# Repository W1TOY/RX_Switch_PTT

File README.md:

# RX Switch PTT — RF-sensing TX/RX antenna switch

A KiCad 9 project for a through-hole TX/RX antenna switch for amateur radio, **1.8–50 MHz, 100 W**.
The radio normally connects to a separate **RX antenna**; on PTT or detected RF it switches to the
**TX antenna** using PIN-style diodes, with a relay bypass for low-loss transmit.

## How it works

- **RF path** — Series/shunt diode switch (D1–D3, 1N4007 as PIN substitutes) with ~120 mA bias,
  RF chokes L1–L4 (~47 µH on FT50-43) and 1 kV MKP/C0G coupling capacitors.
- **PTT** — PTT IN (five RCA inputs in parallel) drives K1 (audio mute + dry-contact PTT OUT)
  and K2, a G2RL-2 relay that bypasses the diode TX path. K2 is always cold-switched because the
  diode path is already conducting.
- **RF sense** — Fast detector (LM311, < 1 µs) forces TX the moment RF appears. RF without PTT is
  treated as a fault: TX is held ~10 s after the last RF and the **RF SENSED** LED lights.
- **RX diode bias** — D3 is reverse-biased from an RF-derived high-voltage doubler
  (HT ≈ 2 × RF peak, clamped at ~220 V), so no separate HV supply is needed.
- **Fail-safe** — K3 (G2RL-2 DPDT) connects RADIO straight to the TX antenna whenever 12 V is
  absent or the RX ANT switch (SW1) is off, fully isolating the switch.
- **Power** — 12 V DC via a 2.1 × 5.5 mm barrel jack (center positive).

> ⚠️ **High voltage:** up to ~220 V DC is present on the HT net during transmit.

## Board

- Two-layer, all through-hole, intended for CNC milling.
- Layout rev 2.0: hybrid layout with 3 mm RF clearances and the RF block at the antenna end.
- Coax (RG58/RG316) solders directly to the board; panel parts (SW1, TX and RF SENSED LEDs) connect via 2.54 mm headers.

## Files

| Path | Contents |
|------|----------|
| `rx_switch_ptt/rx_switch_ptt.kicad_pro` | KiCad project (open this) |
| `rx_switch_ptt/rx_switch_ptt.kicad_sch` | Schematic, with detailed design notes |
| `rx_switch_ptt/rx_switch_ptt.kicad_pcb` | PCB layout |
| `rx_switch_ptt/rx_switch_ptt.kicad_sym` | Project symbol library |
| `rx_switch_ptt/rx_switch_ptt.pretty/` | Custom footprints (coax pads, RCA jacks, T50 toroid, PIN diodes, …) |

The schematic text notes cover part choices, bias calculations, relay pinouts and test
procedures. Read them before building.

## Before use

- Verify relay pinouts and RCA jack footprints against datasheets and real parts.
- Set the radio's TX delay to ≥ 10 ms so K2 closes before full power.
- Test a 10 s RF-sense hold at 100 W into a dummy load, checking diode temperature and SWR,
  including on 160 m.

73 de W1TOY

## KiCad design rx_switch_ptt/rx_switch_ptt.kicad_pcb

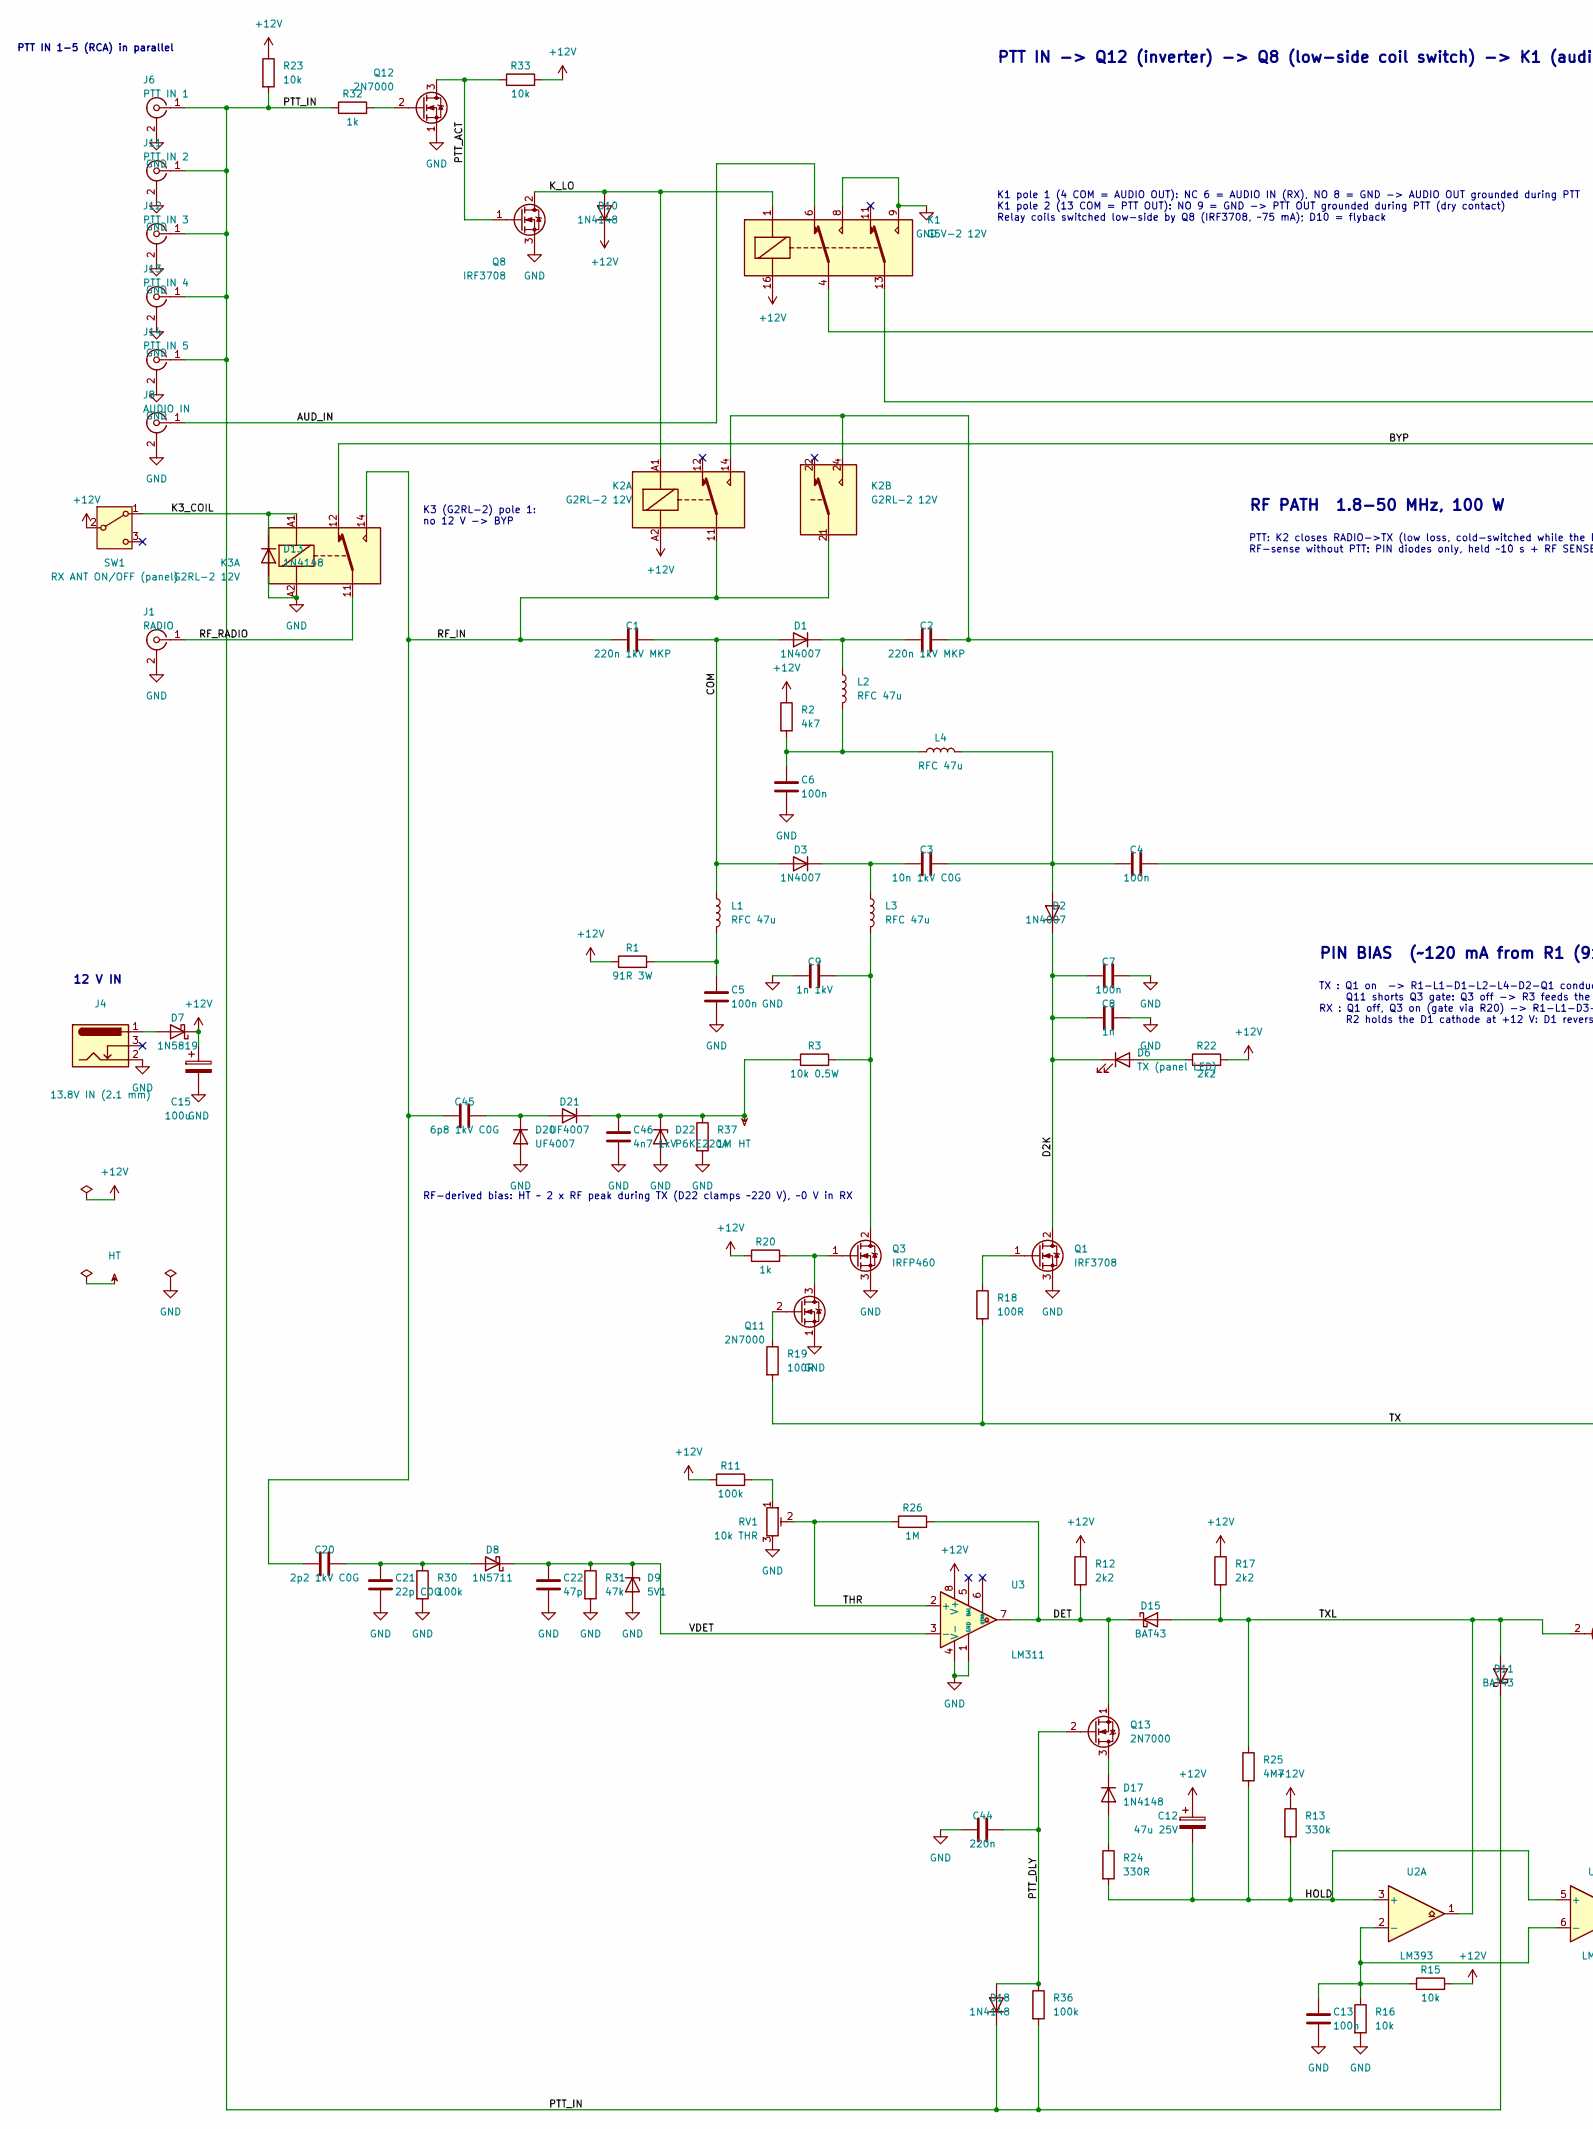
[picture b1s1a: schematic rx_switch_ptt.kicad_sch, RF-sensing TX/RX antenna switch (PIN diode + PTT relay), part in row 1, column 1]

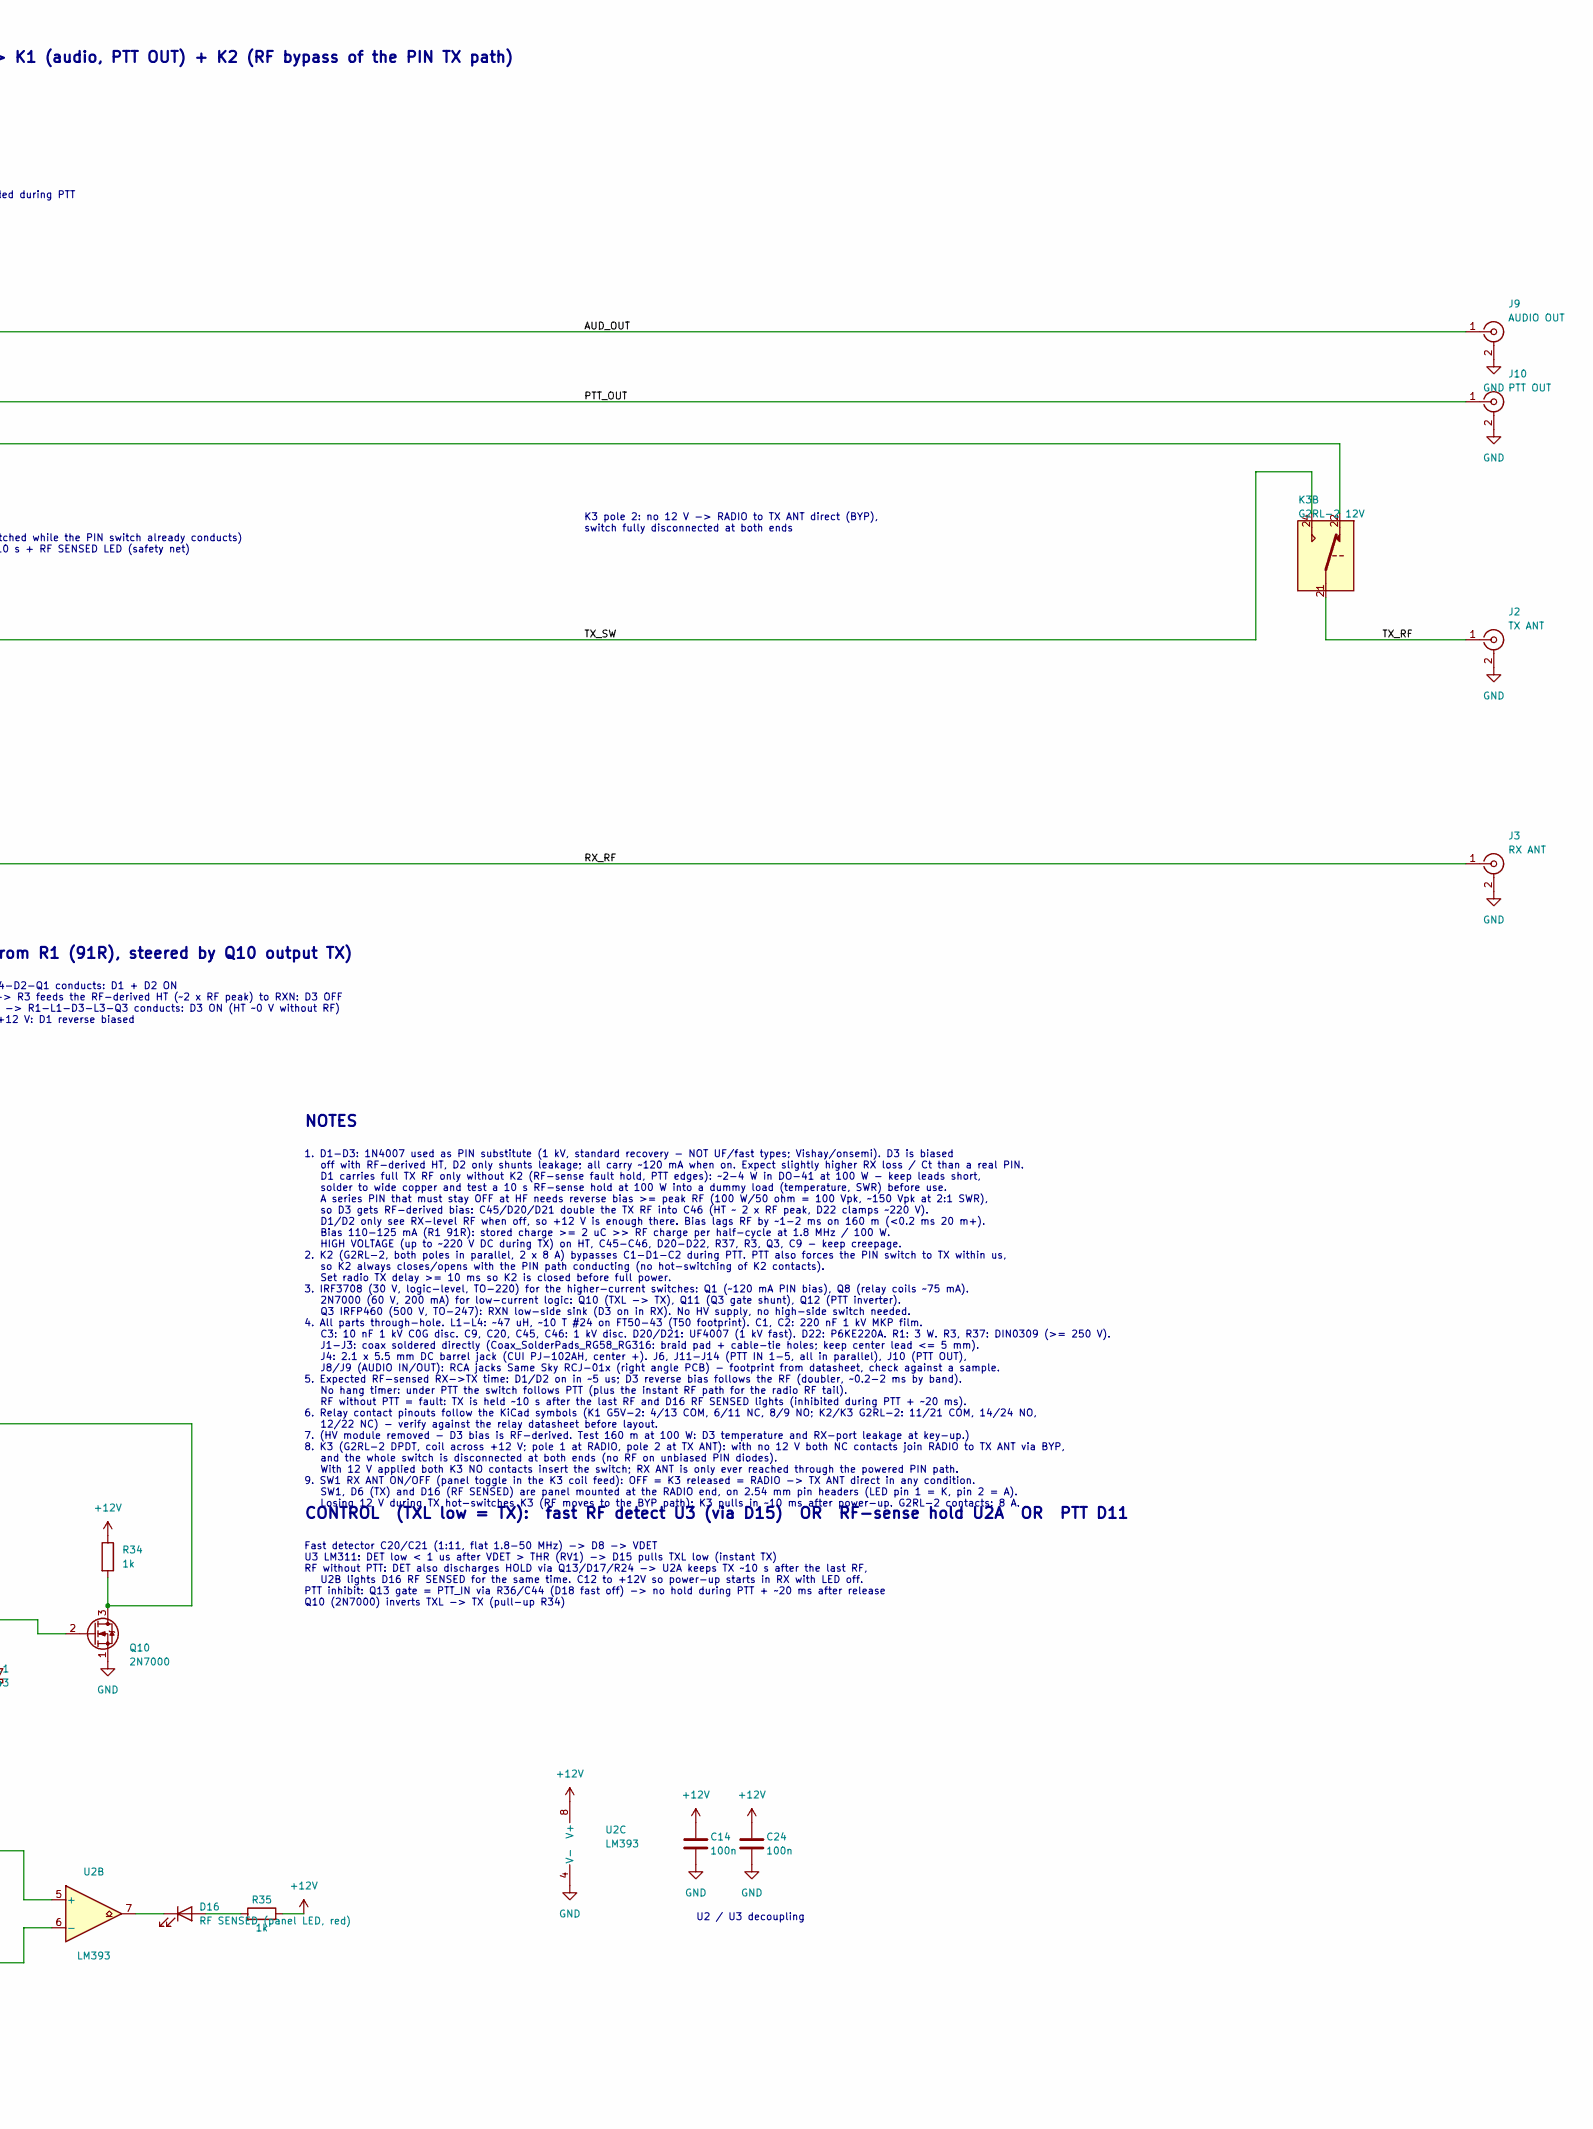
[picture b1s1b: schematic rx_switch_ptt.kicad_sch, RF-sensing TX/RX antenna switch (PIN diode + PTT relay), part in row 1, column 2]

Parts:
C1, C2: 220n 1kV MKP; C_Rect_L18.0mm_W8.0mm_P15.00mm_FKS3_FKP3
C3: 10n 1kV C0G; C_Disc_D7.5mm_W5.0mm_P5.00mm
C4, C5, C6, C7, C13, C14, C24: 100n; C_Disc_D5.0mm_W2.5mm_P5.00mm
C8: 1n; C_Disc_D5.0mm_W2.5mm_P5.00mm
C9: 1n 1kV; C_Disc_D7.5mm_W5.0mm_P5.00mm
C12: 47u 25V; CP_Radial_D6.3mm_P2.50mm
C15: 100u; CP_Radial_D6.3mm_P2.50mm
C20: 2p2 1kV C0G; C_Disc_D7.5mm_W5.0mm_P5.00mm
C21: 22p C0G; C_Disc_D5.0mm_W2.5mm_P5.00mm
C22: 47p; C_Disc_D5.0mm_W2.5mm_P5.00mm
C44: 220n; C_Disc_D5.0mm_W2.5mm_P5.00mm
C45: 6p8 1kV C0G; C_Disc_D7.5mm_W5.0mm_P5.00mm
C46: 4n7 1kV; C_Disc_D7.5mm_W5.0mm_P5.00mm
D1, D2, D3: 1N4007; D_DO-41_SOD81_P10.16mm_Horizontal
D6: TX (panel LED); PinHeader_1x02_P2.54mm_Vertical
D7: 1N5819; D_DO-41_SOD81_P10.16mm_Horizontal
D8: 1N5711; D_DO-35_SOD27_P2.54mm_Vertical_AnodeUp
D9: 5V1; D_DO-35_SOD27_P2.54mm_Vertical_AnodeUp
D10, D13, D17, D18: 1N4148; D_DO-35_SOD27_P2.54mm_Vertical_AnodeUp
D11, D15: BAT43; D_DO-35_SOD27_P2.54mm_Vertical_AnodeUp
D16: RF SENSED (panel LED, red); PinHeader_1x02_P2.54mm_Vertical
D20, D21: UF4007; D_DO-41_SOD81_P10.16mm_Horizontal
D22: P6KE220A; D_DO-15_P10.16mm_Horizontal
J1: RADIO; Coax_SolderPads_RG58_RG316
J2: TX ANT; Coax_SolderPads_RG58_RG316
J3: RX ANT; Coax_SolderPads_RG58_RG316
J4: 13.8V IN (2.1 mm); BarrelJack_CUI_PJ-102AH_Horizontal
J6: PTT IN 1; RCA_Jack_SameSky_RCJ-01x_Horizontal
J8: AUDIO IN; RCA_Jack_SameSky_RCJ-01x_Horizontal
J9: AUDIO OUT; RCA_Jack_SameSky_RCJ-01x_Horizontal
J10: PTT OUT; RCA_Jack_SameSky_RCJ-01x_Horizontal
J11: PTT IN 2; RCA_Jack_SameSky_RCJ-01x_Horizontal
J12: PTT IN 3; RCA_Jack_SameSky_RCJ-01x_Horizontal
J13: PTT IN 4; RCA_Jack_SameSky_RCJ-01x_Horizontal
J14: PTT IN 5; RCA_Jack_SameSky_RCJ-01x_Horizontal
K1: G5V-2 12V; Relay_DPDT_Omron_G5V-2
K2, K3: G2RL-2 12V; Relay_DPDT_Omron_G2RL-2
L1, L2, L3, L4: RFC 47u; L_Toroid_T50_Vertical_P6.00mm
Q1, Q8: IRF3708; TO-220-3_Vertical
Q3: IRFP460; TO-247-3_Vertical
Q10, Q11, Q12, Q13: 2N7000; TO-92_Inline
R1: 91R 3W; R_Axial_Power_L20.0mm_W6.4mm_P25.40mm
R2: 4k7; R_Axial_DIN0207_L6.3mm_D2.5mm_P2.54mm_Vertical
R3: 10k 0.5W; R_Axial_DIN0309_L9.0mm_D3.2mm_P12.70mm_Horizontal
R11, R30, R36: 100k; R_Axial_DIN0207_L6.3mm_D2.5mm_P2.54mm_Vertical
R12, R17, R22: 2k2; R_Axial_DIN0207_L6.3mm_D2.5mm_P2.54mm_Vertical
R13: 330k; R_Axial_DIN0207_L6.3mm_D2.5mm_P2.54mm_Vertical
R15, R16, R23, R33: 10k; R_Axial_DIN0207_L6.3mm_D2.5mm_P2.54mm_Vertical
R18, R19: 100R; R_Axial_DIN0207_L6.3mm_D2.5mm_P2.54mm_Vertical
R20, R32, R34, R35: 1k; R_Axial_DIN0207_L6.3mm_D2.5mm_P2.54mm_Vertical
R24: 330R; R_Axial_DIN0207_L6.3mm_D2.5mm_P2.54mm_Vertical
R25: 4M7; R_Axial_DIN0207_L6.3mm_D2.5mm_P2.54mm_Vertical
R26: 1M; R_Axial_DIN0207_L6.3mm_D2.5mm_P2.54mm_Vertical
R31: 47k; R_Axial_DIN0207_L6.3mm_D2.5mm_P2.54mm_Vertical
R37: 1M; R_Axial_DIN0309_L9.0mm_D3.2mm_P12.70mm_Horizontal
RV1: 10k THR; Potentiometer_Bourns_3296W_Vertical
SW1: RX ANT ON/OFF (panel); PinHeader_1x03_P2.54mm_Vertical
U2: LM393; DIP-8_W7.62mm
U3: LM311; DIP-8_W7.62mm

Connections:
+12V: C12.1, C14.1, C15.1, C24.1, D7.1 (K), D10.1 (K), K1.16, K2.A2, R1.1, R2.1, R11.1, R12.1, R13.1, R15.2, R17.1, R20.1, R22.2, R23.1, R33.2, R34.1, R35.2, SW1.2 (B), U2.8 (V+), U3.8 (V+)
/AUD_IN: J8.1 (In), K1.6
/AUD_OUT: J9.1 (In), K1.4
/BYP: K3.12, K3.22
/COM: C1.2, D1.2 (A), D3.2 (A), L1.1
/D2K: C7.1, C8.1, D2.1 (K), D6.1 (K), Q1.2 (D)
/DET: D15.1 (K), Q13.1 (S), R12.2, R26.2, U3.7
/HOLD: C12.2, R13.2, R24.2, R25.2, U2.3 (+), U2.5 (+)
/K3_COIL: D13.1 (K), K3.A1, SW1.1 (A)
/K_LO: D10.2 (A), K1.1, K2.A1, Q8.2 (D)
/PTT_ACT: Q8.1 (G), Q12.3 (D), R33.1
/PTT_DLY: C44.2, D18.2 (A), Q13.2 (G), R36.1
/PTT_IN: D11.1 (K), D18.1 (K), J6.1 (In), J11.1 (In), J12.1 (In), J13.1 (In), J14.1 (In), R23.2, R32.1, R36.2
/PTT_OUT: J10.1 (In), K1.13
/RF_IN: C1.1, C20.1, C45.1, K2.11, K2.21, K3.14
/RF_RADIO: J1.1 (In), K3.11
/RX_RF: C4.2, J3.1 (In)
/THR: R26.1, RV1.2, U3.2 (+)
/TX: Q10.3 (D), R18.2, R19.2, R34.2
/TXL: D11.2 (A), D15.2 (A), Q10.2 (G), R17.2, R25.1, U2.1
/TX_RF: J2.1 (In), K3.21
/TX_SW: C2.2, K2.14, K2.24, K3.24
/VDET: C22.1, D8.1 (K), D9.1 (K), R31.1, U3.3 (-)
GND: C5.2, C6.2, C7.2, C8.2, C9.1, C13.2, C14.2, C15.2, C21.2, C22.2, C24.2, C44.1, C46.2, D9.2 (A), D13.2 (A), D20.2 (A), D22.2 (A), J1.2 (Ext), J2.2 (Ext), J3.2 (Ext), J4.2, J6.2 (Ext), J8.2 (Ext), J9.2 (Ext), J10.2 (Ext), J11.2 (Ext), J12.2 (Ext), J13.2 (Ext), J14.2 (Ext), K1.8, K1.9, K3.A2, Q1.3 (S), Q3.3 (S), Q8.3 (S), Q10.1 (S), Q11.1 (S), Q12.1 (S), R16.2, R30.2, R31.2, R37.2, RV1.3, U2.4 (V-), U3.1 (GND), U3.4 (V-)
HT: C46.1, D21.1 (K), D22.1 (K), R3.1, R37.1
unnamed: C5.1, L1.2, R1.2
unnamed: C6.1, L2.2, L4.1, R2.2
unnamed: C2.1, D1.1 (K), L2.1
unnamed: C3.2, C4.1, D2.2 (A), L4.2
unnamed: C3.1, D3.1 (K), L3.1
unnamed: D6.2 (A), R22.1
unnamed: D7.2 (A), J4.1
unnamed: C20.2, C21.1, D8.2 (A), R30.1
unnamed: D16.2 (A), R35.1
unnamed: D16.1 (K), U2.7
unnamed: D17.2 (A), R24.1
unnamed: D17.1 (K), Q13.3 (D)
unnamed: C45.2, D20.1 (K), D21.2 (A)
unnamed: Q1.1 (G), R18.1
unnamed: C9.2, L3.2, Q3.2 (D), R3.2
unnamed: Q3.1 (G), Q11.3 (D), R20.2
unnamed: Q11.2 (G), R19.1
unnamed: Q12.2 (G), R32.2
unnamed: R11.2, RV1.1
unnamed: C13.1, R15.1, R16.1, U2.2 (-), U2.6 (-)

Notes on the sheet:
PTT IN -> Q12 (inverter) -> Q8 (low-side coil switch) -> K1 (audio, PTT OUT) + K2 (RF bypass of the PIN TX path)
PTT IN 1-5 (RCA) in parallel
K1 pole 1 (4 COM = AUDIO OUT): NC 6 = AUDIO IN (RX), NO 8 = GND -> AUDIO OUT grounded during PTT K1 pole 2 (13 COM = PTT OUT): NO 9 = GND -> PTT OUT grounded during PTT (dry contact) Relay coils switched low-side by Q8 (IRF3708, ~75 mA); D10 = flyback
RF PATH 1.8-50 MHz, 100 W
PTT: K2 closes RADIO->TX (low loss, cold-switched while the PIN switch already conducts) RF-sense without PTT: PIN diodes only, held ~10 s + RF SENSED LED (safety net)
K3 (G2RL-2) pole 1: no 12 V -> BYP
K3 pole 2: no 12 V -> RADIO to TX ANT direct (BYP), switch fully disconnected at both ends
PIN BIAS (~120 mA from R1 (91R), steered by Q10 output TX)
TX : Q1 on -> R1-L1-D1-L2-L4-D2-Q1 conducts: D1 + D2 ON Q11 shorts Q3 gate: Q3 off -> R3 feeds the RF-derived HT (~2 x RF peak) to RXN: D3 OFF RX : Q1 off, Q3 on (gate via R20) -> R1-L1-D3-L3-Q3 conducts: D3 ON (HT ~0 V without RF) R2 holds the D1 cathode at +12 V: D1 reverse biased
RF-derived bias: HT ~ 2 x RF peak during TX (D22 clamps ~220 V), ~0 V in RX
CONTROL (TXL low = TX): fast RF detect U3 (via D15) OR RF-sense hold U2A OR PTT D11
Fast detector C20/C21 (1:11, flat 1.8-50 MHz) -> D8 -> VDET U3 LM311: DET low < 1 us after VDET > THR (RV1) -> D15 pulls TXL low (instant TX) RF without PTT: DET also discharges HOLD via Q13/D17/R24 -> U2A keeps TX ~10 s after the last RF, U2B lights D16 RF SENSED for the same time. C12 to +12V so 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
U2 / U3 decoupling
12 V IN
NOTES
1. D1-D3: 1N4007 used as PIN substitute (1 kV, standard recovery - NOT UF/fast types; Vishay/onsemi). D3 is biased off with RF-derived HT, D2 only shunts leakage; all carry ~120 mA when on. Expect slightly higher RX loss / Ct than a real PIN. D1 carries full TX RF only without K2 (RF-sense fault ho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

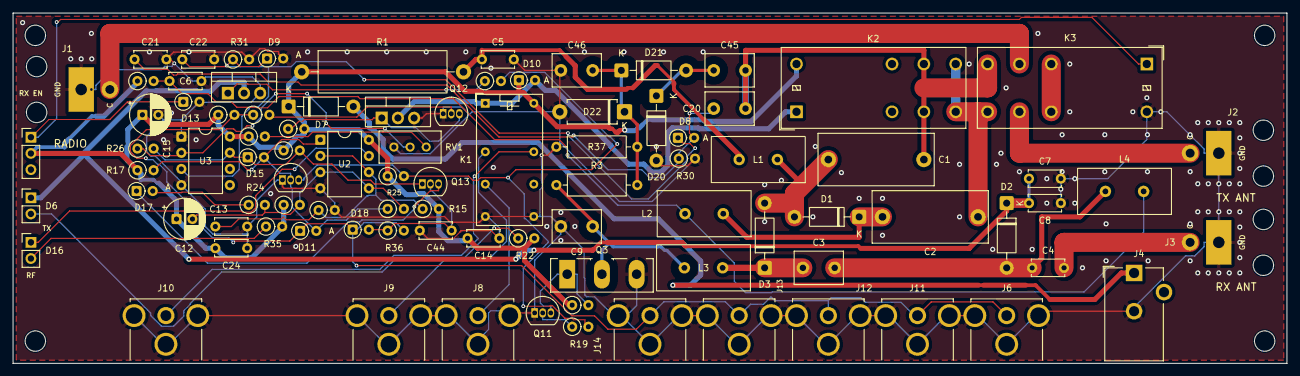
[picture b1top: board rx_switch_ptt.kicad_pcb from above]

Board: 2 copper layers, 200.0 x 55.0 mm, 96 parts (0 on the bottom side), 45 nets.

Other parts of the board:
H1, H2, H3, H4: MountingHole_3.2mm_M3
